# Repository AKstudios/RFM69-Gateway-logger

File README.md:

# RFM69-Gateway-logger
This is a gateway logger for the RFM69 FSK module. Incoming wireless data is saved on microSD card with time stamps from onboard RTC.

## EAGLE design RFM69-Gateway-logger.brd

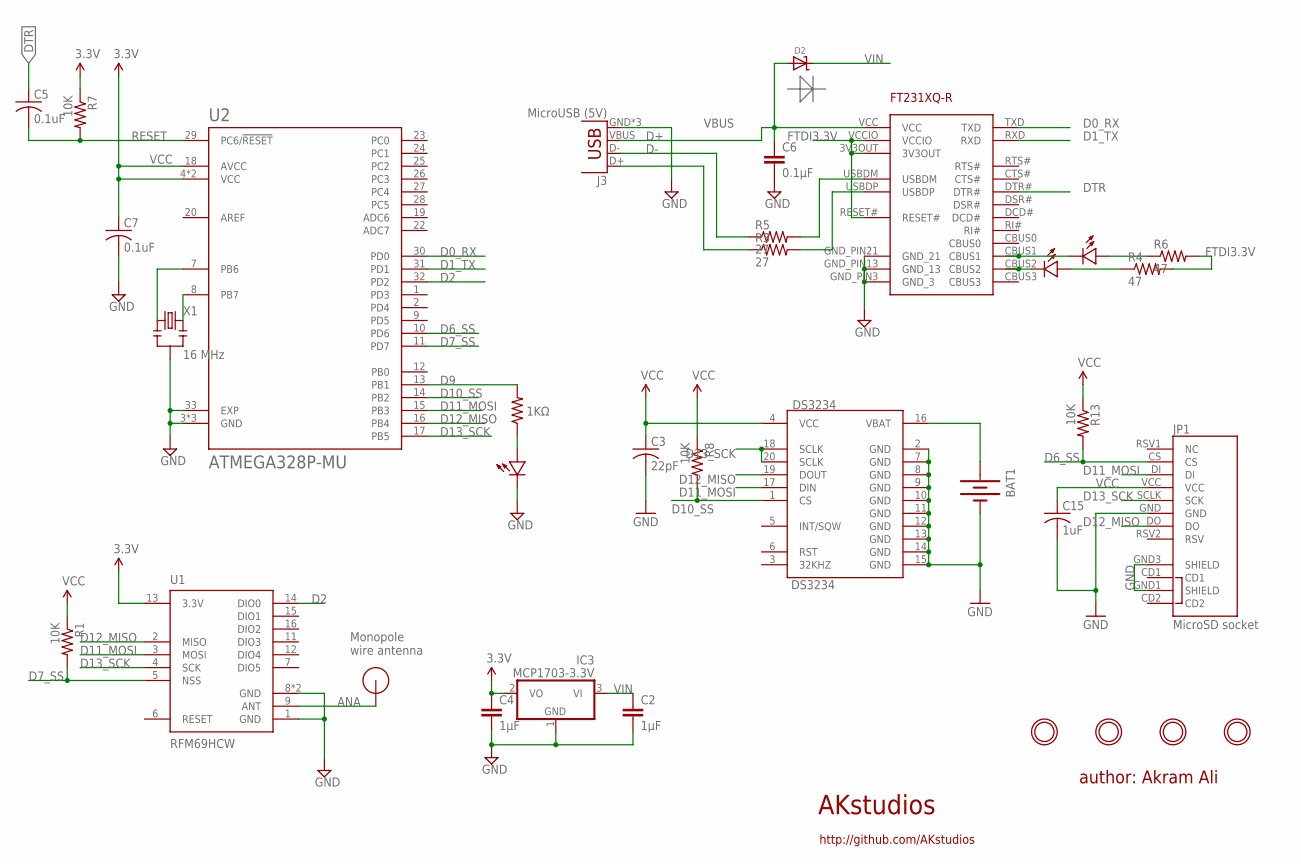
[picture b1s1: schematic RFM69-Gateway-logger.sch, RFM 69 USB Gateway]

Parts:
BAT1: BATTERY12MM; BATTCON_12MM; MPN 3000
C2, C4: 1μF; 0805; MPN CC0805ZRY5V8BB105
C3: 22pF; C0402
C5, C7: 0.1uF; C0402
C6: 0.1μF; 0805; MPN CC0805KRX7R9BB104
C15: 1uF; C0402
D2: MICROBUILDER_DIODE-SCHOTTKYSOD-123; MICROBUILDER_SOD-123
DS3234: DS3234; MPN DS3234S#
FT231XQ-R: FT231XQ-R; FTDI_FT231XQ-R_PACKAGE; MPN FT231XQ-R
IC3: MCP1703-3.3V; SOT23; MPN MCP1703T-2502E/CB
J3: MicroUSB (5V); USB-MICROB; MPN CONN-09505
JP1: MicroSD socket; MICRO-SD-SOCKET-PP
R1, R7, R8, R13: 10K; R0402
R2: 1KΩ; 0805; MPN RC0805FR-071KL
R3, R5: 27; R0402
R4, R6: 47; R0402
RX: Green; 0805-LED; MPN LG R971-KN-1
TX: Red; 0805-LED; MPN LG R971-KN-1
U1: RFM69HCW; RFM69HCW-XXXS2; MPN RFM69HW
U2: ATMEGA328P-MU; QFN50P500X500X100-33N; MPN ATmega328P-MU
U$1, U$5, U$7, U$8: MOUNTINGHOLE2.0; MOUNTINGHOLE_2.0_PLATED
U$2: Status; 0805-LED; MPN LG R971-KN-1
U$6: RFM12B_ANTENNA; RFM12B-ANTENNA
X1: 16 MHz; RESONATOR-SMD; MPN CSTCE16M0V53-R0

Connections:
ANA: U1.9 (ANT), U$6.P$1
D0_RX: FT231XQ-R.TXD, U2.30 (PD0)
D1_TX: FT231XQ-R.RXD, U2.31 (PD1)
D2: U1.14 (DIO0), U2.32 (PD2)
D6_SS: JP1.CS, R13.2, U2.10 (PD6)
D7_SS: R1.2, U1.5 (NSS), U2.11 (PD7)
D9: R2.2, U2.13 (PB1)
D10_SS: DS3234.1 (CS), R8.2, U2.14 (PB2)
D11_MOSI: DS3234.17 (DIN), JP1.DI, U1.3 (MOSI), U2.15 (PB3)
D12_MISO: DS3234.19 (DOUT), JP1.DO, U1.2 (MISO), U2.16 (PB4)
D13_SCK: DS3234.18 (SCLK), DS3234.20 (SCLK), JP1.SCLK (SCK), U1.4 (SCK), U2.17 (PB5)
D+: J3.D+, R3.1
D-: J3.D-, R5.1
DTR: C5.1, FT231XQ-R.DTR#
FTDI3.3V: FT231XQ-R.3V3OUT, FT231XQ-R.RESET#, FT231XQ-R.VCCIO, R4.2, R6.2
GND: BAT1.GND (-), C2.2, C3.2, C4.2, C6.2, C7.2, C15.2, DS3234.2 (GND), DS3234.7 (GND), DS3234.8 (GND), DS3234.9 (GND), DS3234.10 (GND), DS3234.11 (GND), DS3234.12 (GND), DS3234.13 (GND), DS3234.14 (GND), DS3234.15 (GND), FT231XQ-R.GND_PIN3 (GND_3), FT231XQ-R.GND_PIN13 (GND_13), FT231XQ-R.GND_PIN21 (GND_21), IC3.1 (GND), J3.GND, J3.MT1 (GND), J3.MT2 (GND), JP1.GND, JP1.GND1 (SHIELD), JP1.GND3 (SHIELD), U1.1 (GND), U1.8 (GND), U1.10 (GND), U2.3 (GND), U2.5 (GND), U2.21 (GND), U2.33 (EXP), U$2.MINUS, X1.2
unnamed: U2.7 (PB6), X1.1
unnamed: R2.1, U$2.PLUS
unnamed: BAT1.PWR@1 (+), DS3234.16 (VBAT)
unnamed: FT231XQ-R.USBDM, R5.2
unnamed: FT231XQ-R.USBDP, R3.2
unnamed: FT231XQ-R.CBUS1, RX.MINUS
unnamed: FT231XQ-R.CBUS2, TX.MINUS
unnamed: R4.1, TX.PLUS
unnamed: R6.1, RX.PLUS
unnamed: U2.8 (PB7), X1.3
RESET: C5.2, R7.2, U2.29 (PC6/!RESET)
VBUS: C6.1, D2.A, FT231XQ-R.VCC, J3.VBUS
VCC: C3.1, C4.1, C7.1, C15.1, DS3234.4 (VCC), IC3.2 (VO), JP1.VCC, R1.1, R7.1, R8.1, R13.1, U1.13 (3.3V), U2.4 (VCC), U2.6 (VCC), U2.18 (AVCC)
VIN: C2.1, D2.C, IC3.3 (VI)

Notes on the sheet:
AKstudios
author: Akram Ali
http://github.com/AKstudios
Monopole wire antenna

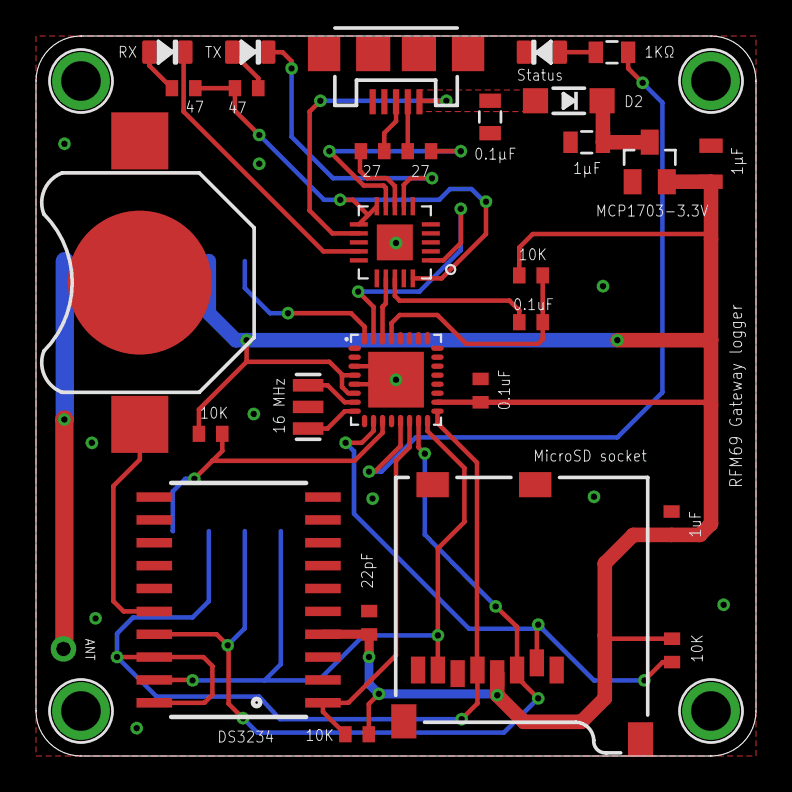
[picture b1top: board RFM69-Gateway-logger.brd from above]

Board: 2 copper layers, 40.0 x 40.0 mm, 34 parts (1 on the bottom side), 30 nets.

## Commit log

2017-05-23 :tada: Added .gitattributes & .gitignore files
2017-05-23 init
2017-05-23 Adjusted antenna & silkscreen
2017-05-23 Minor adjustments
2017-05-23 Silkscreen update
2017-05-23 ANT pad adjusted
    some GND pours adjusted

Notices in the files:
parts and their libraries:
SparkFun-Connectors: Licensing: Creative Commons ShareAlike 4.0 International - https://creativecommons.org/licenses/by-sa/4.0
